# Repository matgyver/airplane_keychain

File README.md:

# airplane_keychain
A simple aircraft keychain designed to be easy to solder.

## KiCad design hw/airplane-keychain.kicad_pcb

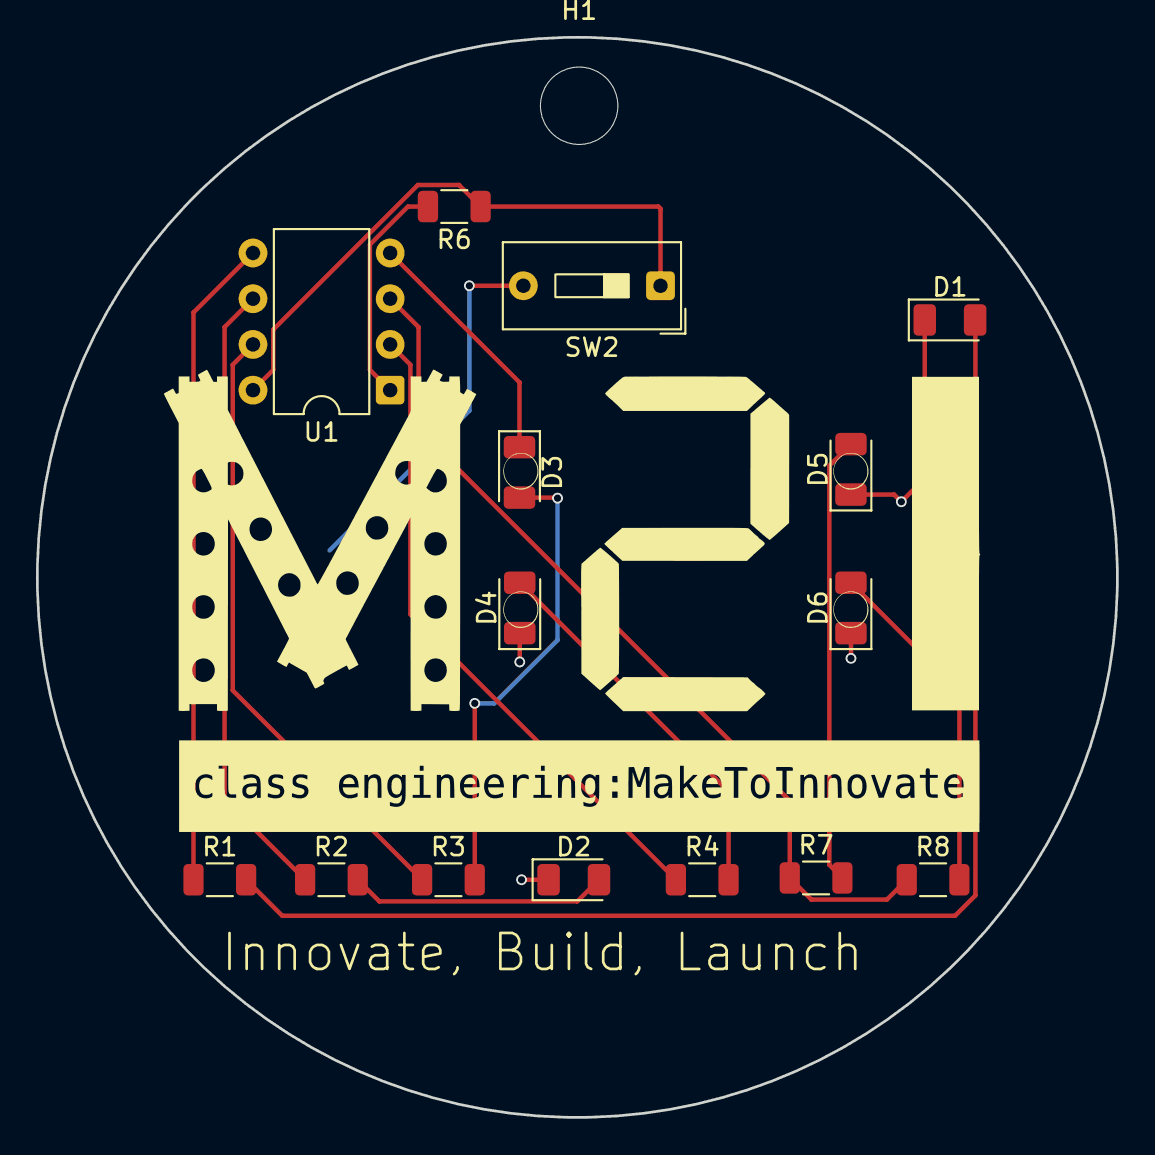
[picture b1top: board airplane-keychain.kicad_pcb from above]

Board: 2 copper layers, 60.0 x 60.0 mm, 17 parts (1 on the bottom side), 15 nets.

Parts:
BT1: Battery_Cell; BatteryHolder_Keystone_1058_1x2032
D1, D3, D4: Red; LED_1206_3216Metric
D2, D5, D6: Amber; LED_1206_3216Metric
H1: MountingHole; MountingHole_4.3mm_M4
R1, R2, R3, R4, R7, R8: 120; R_1206_3216Metric
R6: 10k; R_1206_3216Metric
SW2: SPST; SW_DIP_SPSTx01_Slide_9.78x4.72mm_W7.62mm_P2.54mm
U1: ATtiny85-20P; DIP-8_W7.62mm

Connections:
GND: BT1.2 (-), D1.1 (K), D2.1 (K), D3.1 (K), D4.1 (K), D5.1 (K), D6.1 (K), U1.4 (GND)
unnamed: BT1.1 (+), SW2.2
unnamed: D1.2 (A), R1.2
unnamed: D2.2 (A), R2.2
unnamed: D3.2 (A), R3.2
unnamed: D4.2 (A), R4.2
unnamed: D5.2 (A), R7.2
unnamed: D6.2 (A), R8.2
unnamed: R1.1, U1.5 (AREF/PB0)
unnamed: R2.1, U1.6 (PB1)
unnamed: R3.1, U1.7 (PB2)
unnamed: R6.1, SW2.1, U1.8 (VCC)
unnamed: R4.1, U1.2 (XTAL1/PB3)
unnamed: R7.1, R8.1, U1.3 (XTAL2/PB4)
unnamed: R6.2, U1.1 (~RESET/PB5)

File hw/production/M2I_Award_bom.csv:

Designator,Footprint,Quantity,Value,LCSC Part #
BT1,BatteryHolder_Keystone_1058_1x2032,1,Battery_Cell,C5470546
"D1, D3, D4",1206,3,Red,C49018
"D2, D5, D6",1206,3,Amber,C5478408
"R1, R2, R3, R4, R7, R8",1206,6,120,C17909
R6,1206,1,10k,C1489

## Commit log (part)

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2017-03-27 First draft
    First draft of schedmatic and board
2017-03-27 Tests with board outline
    Not going so well :(
2017-03-27 board outline
2017-04-02 added current limiting resistors
    swapped out battery connector
2017-04-03 update to board
2017-04-03 board update
2017-04-07 Added second battery
    Changed some footprints
2017-04-14 Added aircraft outline
    Changed board edges to aircraft outline
2017-04-14 Update to schematic
    Minor part changes
2017-04-15 First run routed board
2017-04-15 Second trace run
    Second attempt to routing and layout
2017-04-15 Switch to new PCB cutout
    Switch to new PCB cutout. Added files for generating boards using
    OpenSCAD. Cleaned up some files.
2017-04-18 minor updates
    added BOM
2017-04-29 Minor BOM update, FW initial version
2017-05-01 Final for RevA
    Final changes based on prototype testing for Rev A.
2023-04-15 Update to newer KiCad
2023-07-25 Update to keychain
2023-08-01 KiCad update
2023-12-08 minor update
2023-12-08 Initial update for ISGC model
2023-12-08 Updates to logo
2023-12-08 Update for ISGC
2023-12-11 Added Gerbers
2023-12-11 Fixed gerbers
2024-02-18 Final update
2024-03-03 slight change
2024-03-03 Change to FW code
2024-03-03 Update airplane FW
2024-03-09 Minor
2024-03-09 Redo on PCB added mounting holes
2024-03-14 Added M2I Logo
    Added logo, generated Gerbers and BOM for manufacturing
2024-03-21 Minor edits to page details
2024-12-24 cahce
2025-03-27 Rev B
    Removed some components
2025-03-27 Added gerber files
2025-04-09 Added Gerber
2025-04-25 M2I Version
2025-04-25 draft
2025-06-07 cleanup
2025-06-16 M2I Badge first run
2025-09-08 Added BOM
2025-09-11 Minor fix
2025-12-02 Production Run
2025-12-06 CIAS update
2025-12-13 Switched to PlatformIO
    Using the Sparkfun USB programmer under PlatformIO and MacOS works with no issues. Moved to PlatformIO for future development.
2026-04-23 Minor change for S26
